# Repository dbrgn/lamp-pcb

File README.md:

# Lamp PCB

PCB for a 3D printable lamp.

https://forum.coredump.ch/t/3d-gedruckte-lampe/194

## License

CC BY-SA

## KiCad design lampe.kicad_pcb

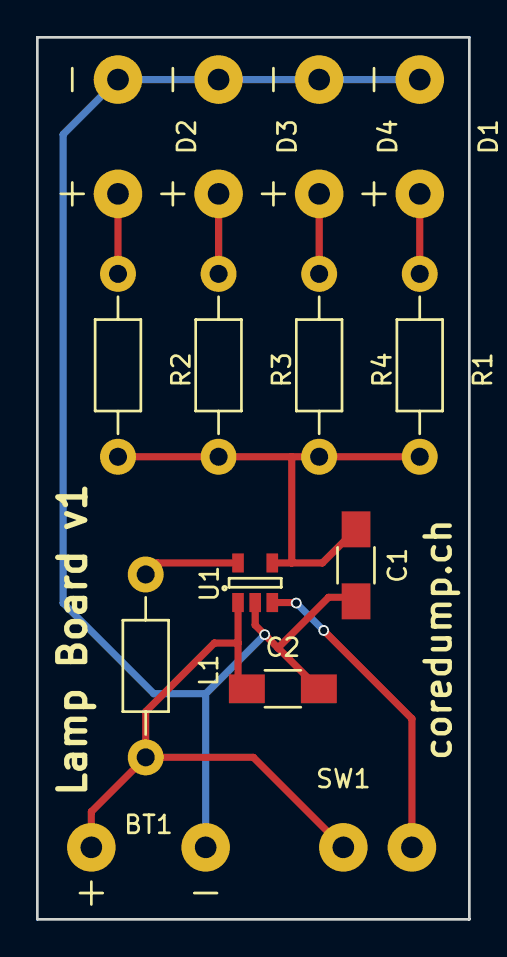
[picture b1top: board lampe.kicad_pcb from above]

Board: 2 copper layers, 24.0 x 49.0 mm, 14 parts (0 on the bottom side), 9 nets.

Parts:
BT1: Bat; Battery
C1, C2: 2.2μF; C_1206_HandSoldering
D1, D2, D3, D4: LED; LED-Pads
L1: 10μH; Resistor_Horizontal_RM10mm
R1, R2, R3, R4: 2.2Ω; Resistor_Horizontal_RM10mm
SW1: Switch; Switch-Pins-2-3
U1: MAX1724; SOT-23-5

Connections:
/2.4V: BT1.1, C2.1, L1.2, SW1.2, U1.1
/3.3V: C1.1, R1.2, R2.2, R3.2, R4.2, U1.4
GND: BT1.2, C1.2, C2.2, D1.1, D2.1, D3.1, D4.1, U1.2
unnamed: D1.2, R1.1
unnamed: D2.2, R2.1
unnamed: D3.2, R3.1
unnamed: D4.2, R4.1
unnamed: L1.1, U1.5
unnamed: SW1.3, U1.3

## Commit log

2016-08-12 Initial version
2016-08-12 Add README
2016-08-12 Add picture
